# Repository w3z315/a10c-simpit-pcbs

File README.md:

# My A10C SimPit PCB collection

Welcome to the A10C Simpit Projects repository! This repository contains all the PCB designs and DCS-Bios Arduino code for various components of an A10C Simpit, currently including the UFC (Up-Front Controller) and MFCD (Multi-Function Color Display).

## Sponsorship
Thank you so much PCBWay.com for sponsoring parts of this project! I was genuinely surprised by how quickly the PCBs arrived - in just 9 days, without even opting for the very express shipping variant. The quality is outstanding, and the PCBs work flawlessly in my setup. It's been a fantastic experience, from design submission to receiving the boards ready for assembly.

## Projects

### UFC (Up-Front Controller)
- **[PCB Design](./ufc/pcb)**: Schematic, layout files, and Bill of Materials (BOM) for the UFC PCB.
- **[Arduino Code](./ufc/arduino)**: Source code and libraries for the UFC Arduino project.

### MFCD (Multi-Function Color Display)
- **[PCB Design](./mfcd/pcb)**: Schematic, layout files, and Bill of Materials (BOM) for the MFCD PCB.
- **[Arduino Code](./mfcd/arduino)**: Source code and libraries for the MFCD Arduino project.

## Getting Started

To get started with any of the projects, navigate to the respective directories for detailed instructions and files.

### Prerequisites

- [KiCad ^8.0](https://www.kicad.org/) for viewing and editing PCB files.
- [PlatformIO](https://platformio.org/)
- [DCS-BIOS - Skunkworks Fork](https://github.com/DCS-Skunkworks/dcs-bios)

### Installation

1. Clone the repository:
    ```sh
    git clone https://github.com/w3z315/a10c-simpit-pcbs.git
    cd a10c-simpit-pcbs
    ```

2. Follow the instructions in the respective project directories to set up the PCB or Arduino code.

## Documentation

Additional documentation can be found in the wiki.

## Contributing

Contributions are welcome! 

## License

This project is licensed under the GPL 3 License. See the [LICENSE](./LICENSE) file for details.

## Acknowledgments

- Thanks to the open-source community for providing the tools and resources that made this project possible. (Winks to Kicad 8!)
- PCBWay.com for their sponsorship and assistance.
- A shoutout to all the DIYers and hobbyists who inspire me every day.
- TheWarthogProject.com - dude, you're amazing!

---

Feel free to reach out if you have any questions or need further assistance. Happy building!

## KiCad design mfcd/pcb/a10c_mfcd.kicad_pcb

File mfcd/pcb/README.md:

# MFCD (Multi-Function-Color-Display) PCB

This one is still work in progress.

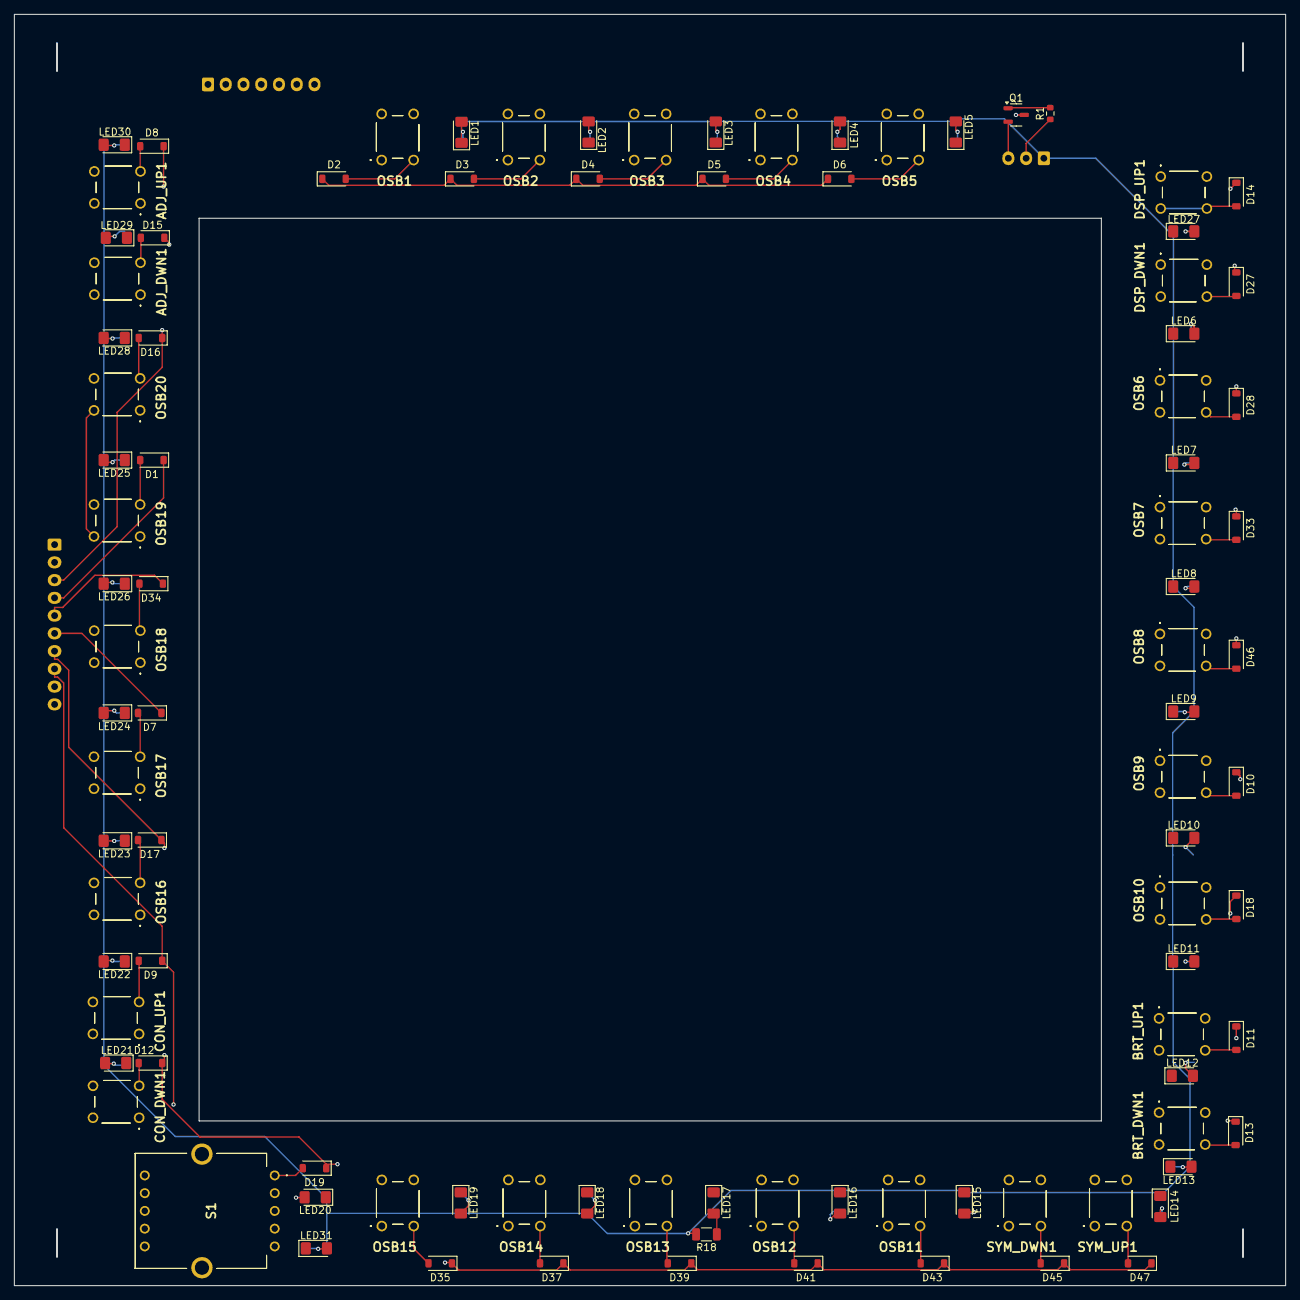
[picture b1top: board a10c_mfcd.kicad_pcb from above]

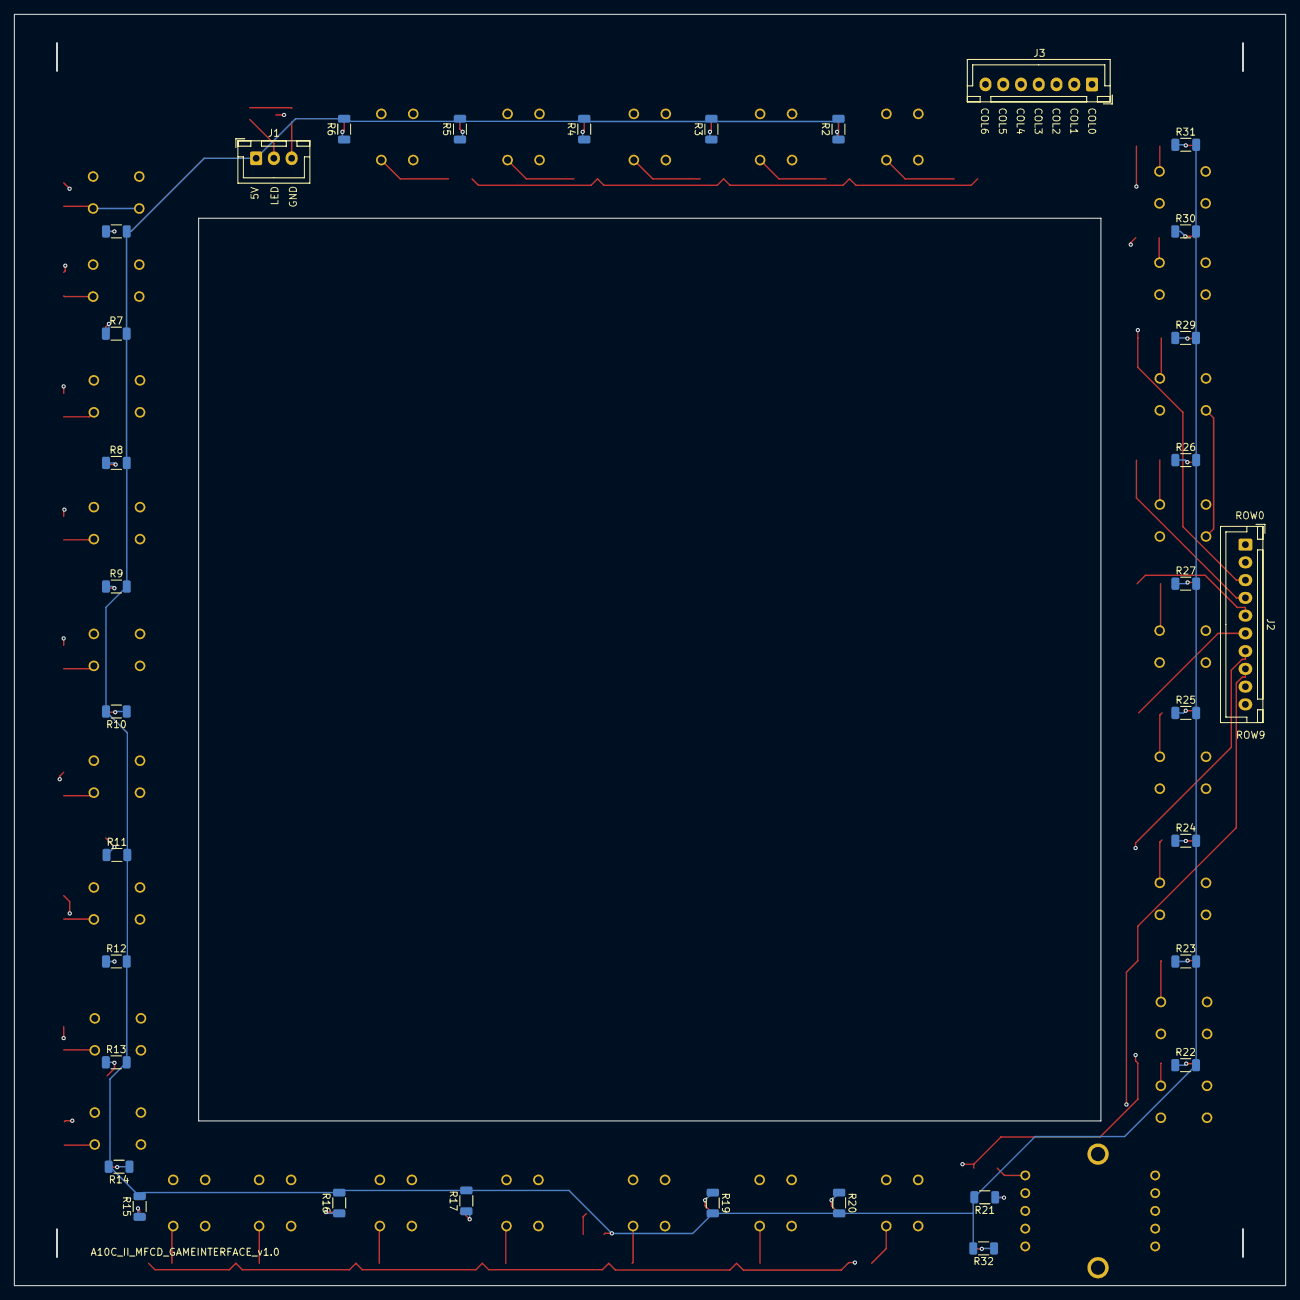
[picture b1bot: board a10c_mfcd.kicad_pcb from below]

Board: 4 copper layers, 179.0 x 179.0 mm, 129 parts (33 on the bottom side), 84 nets.

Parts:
ADJ_DWN1: Switch; 18259671
ADJ_UP1: Switch; 18259671
BRT_DWN1: Switch; 18259671
BRT_UP1: Switch; 18259671
CON_DWN1: Switch; 18259671
CON_UP1: Switch; 18259671
D1, D2, D3, D4, D5, D6, D7, D8, D9, D10, D11, D12, D13, D14, D15, D16, D17, D18, D19, D27, D28, D33, D34, D35, D37, D39, D41, D43, D45, D46, D47: D_Small; D_SOD-123
DSP_DWN1: Switch; 18259671
DSP_UP1: Switch; 18259671
J1: Conn_LED; JST_XH_B3B-XH-A_1x03_P2.50mm_Vertical
J2: Conn_ROWS; JST_XH_B10B-XH-A_1x10_P2.50mm_Vertical
J3: Conn_COLS; JST_XH_B7B-XH-A_1x07_P2.50mm_Vertical
LED1, LED2, LED3, LED4, LED5, LED6, LED7, LED8, LED9, LED10, LED11, LED12, LED13, LED14, LED15, LED16, LED17, LED18, LED19, LED20, LED21, LED22, LED23, LED24, LED25, LED26, LED27, LED28, LED29, LED30, LED31: 1206; LED_1206_3216Metric_Pad1.42x1.75mm_HandSolder
OSB1, OSB2, OSB3, OSB4, OSB5, OSB6, OSB7, OSB8, OSB9, OSB10, OSB11, OSB12, OSB13, OSB14, OSB15, OSB16, OSB17, OSB18, OSB19, OSB20: Switch; 18259671
Q1: BC817-25LT1G; SOT-23-3
R1: 1000; R_0603_1608Metric
R2, R3, R4, R5, R6, R7, R8, R9, R10, R11, R12, R13, R14, R15, R16, R17, R18, R19, R20, R21, R22, R23, R24, R25, R26, R27, R28, R29, R30, R31, R32: 270; R_1206_3216Metric
S1: SRBV131502
SYM_DWN1: Switch; 18259671
SYM_UP1: Switch; 18259671

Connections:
5V: J1.1, R2.2, R3.2, R4.2, R5.2, R6.2, R7.2, R8.2, R9.2, R10.2, R11.2, R12.2, R13.2, R14.2, R15.2, R16.2, R17.2, R18.2, R19.2, R20.2, R21.2, R22.2, R23.2, R24.2, R25.2, R26.2, R27.2, R28.2, R29.2, R30.2, R31.2, R32.2
COL0: ADJ_DWN1.1, ADJ_UP1.1, CON_DWN1.1, CON_UP1.1, J3.1, OSB15.1, OSB16.1, OSB17.1, OSB18.1, OSB19.1, OSB20.1
COL1: J3.2, OSB1.1, OSB14.1, S1.2 (NO_1)
COL2: J3.3, OSB2.1, OSB13.1, S1.3 (NO_2)
COL3: J3.4, OSB3.1, OSB12.1, S1.4 (NO_3)
COL4: J3.5, OSB4.1, OSB11.1
COL5: J3.6, OSB5.1, SYM_DWN1.1
COL6: BRT_DWN1.1, BRT_UP1.1, DSP_DWN1.1, DSP_UP1.1, J3.7, OSB6.1, OSB7.1, OSB8.1, OSB9.1, OSB10.1, SYM_UP1.1
GND: J1.3, Q1.2 (EMITTER)
LED: J1.2, R1.1
unnamed: D1.2 (A), OSB19.2
unnamed: D2.2 (A), OSB1.2
unnamed: D2.1 (K), D3.1 (K), D4.1 (K), D5.1 (K), D6.1 (K)
unnamed: D3.2 (A), OSB2.2
unnamed: D4.2 (A), OSB3.2
unnamed: D5.2 (A), OSB4.2
unnamed: D6.2 (A), OSB5.2
unnamed: D7.2 (A), OSB17.2
unnamed: ADJ_UP1.2, D8.2 (A)
unnamed: CON_UP1.2, D9.2 (A)
unnamed: D10.2 (A), OSB9.2
unnamed: BRT_UP1.2, D11.2 (A)
unnamed: CON_DWN1.2, D12.2 (A)
unnamed: BRT_DWN1.2, D13.2 (A)
unnamed: D14.2 (A), DSP_UP1.2
unnamed: ADJ_DWN1.2, D15.2 (A)
unnamed: D16.2 (A), OSB20.2
unnamed: D17.2 (A), OSB16.2
unnamed: D18.2 (A), OSB10.2
unnamed: D19.2 (A), S1.1 (C)
unnamed: D27.2 (A), DSP_DWN1.2
unnamed: D28.2 (A), OSB6.2
unnamed: D33.2 (A), OSB7.2
unnamed: D34.2 (A), OSB18.2
unnamed: D35.2 (A), OSB15.2
unnamed: D37.2 (A), OSB14.2
unnamed: D39.2 (A), OSB13.2
unnamed: D41.2 (A), OSB12.2
unnamed: D43.2 (A), OSB11.2
unnamed: D45.2 (A), SYM_DWN1.2
unnamed: D46.2 (A), OSB8.2
unnamed: D47.2 (A), SYM_UP1.2
unnamed: LED1.1 (K), LED1.2 (A), Q1.3 (COLLECTOR), R2.1
unnamed: LED2.2 (A), R3.1
unnamed: LED3.2 (A), R4.1
unnamed: LED4.2 (A), R5.1
unnamed: LED5.2 (A), R6.1
unnamed: LED6.2 (A), R7.1
unnamed: LED7.2 (A), R8.1
unnamed: LED8.2 (A), R9.1
unnamed: LED9.2 (A), R10.1
unnamed: LED10.2 (A), R11.1
unnamed: LED11.2 (A), R12.1
unnamed: LED12.2 (A), R13.1
unnamed: LED13.2 (A), R14.1
unnamed: LED14.2 (A), R15.1
unnamed: LED15.2 (A), R16.1
unnamed: LED16.2 (A), R17.1
unnamed: LED17.2 (A), R18.1
unnamed: LED18.2 (A), R19.1
unnamed: LED19.2 (A), R20.1
unnamed: LED20.2 (A), R21.1
unnamed: LED21.2 (A), R22.1
unnamed: LED22.2 (A), R23.1
unnamed: LED23.2 (A), R24.1
unnamed: LED24.2 (A), R25.1
unnamed: LED25.2 (A), R26.1
unnamed: LED26.2 (A), R27.1
unnamed: LED27.2 (A), R28.1
unnamed: LED28.2 (A), R29.1
unnamed: LED29.2 (A), R30.1
unnamed: LED30.2 (A), R31.1
unnamed: LED31.2 (A), R32.1
unnamed: Q1.1 (BASE), R1.2
ROW0: D8.1 (K), D14.1 (K), J2.1
ROW1: D15.1 (K), D27.1 (K), J2.2
ROW2: D16.1 (K), D28.1 (K), J2.3
ROW3: D1.1 (K), D33.1 (K), J2.4
ROW4: D34.1 (K), D46.1 (K), J2.5
ROW5: D7.1 (K), D10.1 (K), J2.6
ROW6: D17.1 (K), D18.1 (K), J2.7
ROW7: D9.1 (K), D11.1 (K), J2.8
ROW8: D12.1 (K), D13.1 (K), D19.1 (K), J2.9
ROW9: D35.1 (K), D37.1 (K), D39.1 (K), D41.1 (K), D43.1 (K), D45.1 (K), D47.1 (K), J2.10

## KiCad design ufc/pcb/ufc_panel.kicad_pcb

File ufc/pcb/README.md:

# A-10C Upfront Control Panel (UFC) PCB

Welcome to the repository for my very first PCB design, crafted specifically for an A-10C cockpit simulator project. This project has been a labor of love, a lot of learning, and yes, a few missteps - but that's the beauty of DIY!

## Demo Video

Check out the demo video to see the A10C UFC in action:

## Sponsorship
Thank you so much [PCBWay.com](https://pcbway.com) for sponsoring this project! I was genuinely surprised by how quickly the PCBs arrived - in just 9 days, without even opting for the very express shipping variant. The quality is outstanding, and the PCBs work flawlessly in my setup. It's been a fantastic experience, from design submission to receiving the boards ready for assembly.

## About the Project
The A-10C UFC PCB is for my custom A-10C cockpit control panel.

## Todos:
- [ ] Add more backlight LEDs so the bottom row is better illuminated.
- [ ] Add another yellow LED for the Master Caution to spread out light more evenly.
- [ ] Better connector?

## Arduino Code
You can find the code for the PCB and Arduino Nano at [https://github.com/w3z315/a10c-ufc-arduino](https://github.com/w3z315/a10c-ufc-arduino).

## Repository Contents
Inside this repository, you'll find all the KiCad files used to create the PCB. Feel free to browse through them, use them as a reference, or even contribute to improving the design.

## Images & gifs

)

## Issues and Contributing
If you notice any issues or if you've got suggestions for improvements, don't hesitate to open an issue or a pull request. This project is all about community and collaboration.

## License

This project is licensed under the GNU GPLv3 License - see the [LICENSE](LICENSE) file for details.

## Acknowledgements
- Thanks to the open-source community for providing the tools and resources that made this project possible. (Winks to Kicad 8!)
- PCBWay.com for their sponsorship and assistance.
- A shoutout to all the DIYers and hobbyists who inspire me every day.
- TheWarthogProject.com - dude, you're amazing!

Happy building!

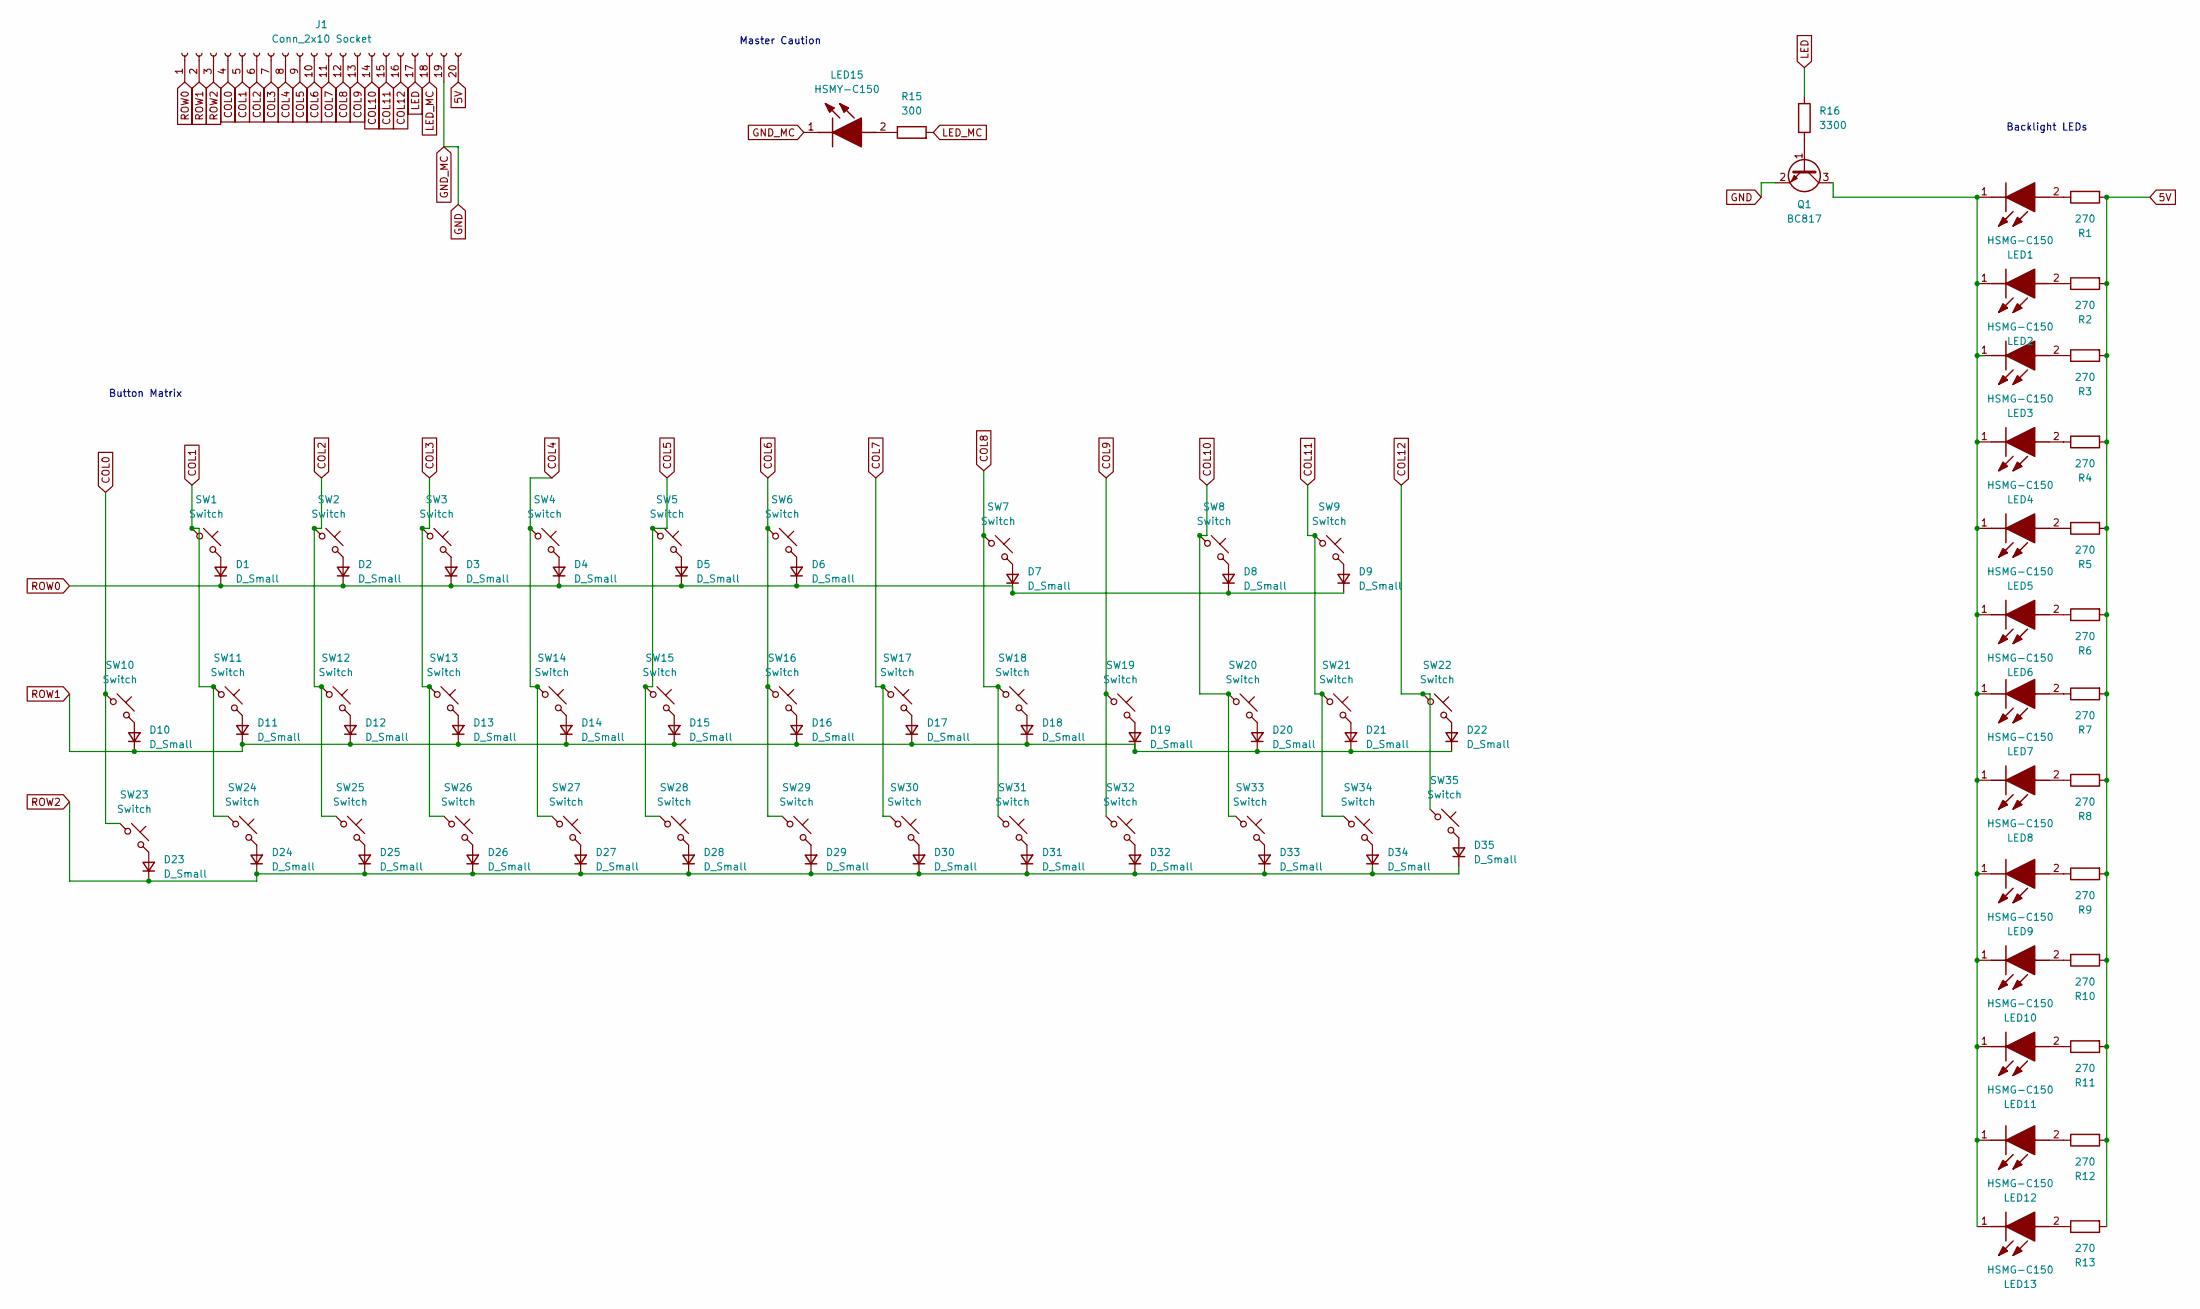
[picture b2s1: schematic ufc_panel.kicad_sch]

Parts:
D1, D2, D3, D4, D5, D6, D7, D8, D9, D10, D11, D12, D13, D14, D15, D16, D17, D18, D19, D20, D21, D22, D23, D24, D25, D26, D27, D28, D29, D30, D31, D32, D33, D34, D35: D_Small; D_SOD-123
J1: Conn_2x10 Socket; PinHeader_1x20_P2.54mm_Vertical
LED1, LED2, LED3, LED4, LED5, LED6, LED7, LED8, LED9, LED10, LED11, LED12, LED13: HSMG-C150; LED_1206_3216Metric_Pad1.42x1.75mm_HandSolder; Mouser Part Number 630-HSMG-C150
LED15: HSMY-C150; LED_1206_3216Metric_Pad1.42x1.75mm_HandSolder; Mouser Part Number 630-HSMY-C150
Q1: BC817; SOT-23
R1, R2, R3, R4, R5, R6, R7, R8, R9, R10, R11, R12, R13: 270; R_1206_3216Metric
R15: 300; R_1206_3216Metric
R16: 3300; R_0603_1608Metric
SW1, SW2, SW3, SW4, SW5, SW6, SW7, SW8, SW9, SW10, SW11, SW12, SW13, SW14, SW15, SW16, SW17, SW18, SW19, SW20, SW21, SW22, SW23, SW24, SW25, SW26, SW27, SW28, SW29, SW30, SW31, SW32, SW33, SW34, SW35: Switch; SW_PUSH_6mm_H4.3mm_INT_CONNECTED

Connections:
5V: J1.20, R1.2, R2.2, R3.2, R4.2, R5.2, R6.2, R7.2, R8.2, R9.2, R10.2, R11.2, R12.2, R13.2
COL0: J1.4, SW10.1, SW23.1
COL1: J1.5, SW1.1, SW11.1, SW24.1
COL2: J1.6, SW2.1, SW12.1, SW25.1
COL3: J1.7, SW3.1, SW13.1, SW26.1
COL4: J1.8, SW4.1, SW14.1, SW27.1
COL5: J1.9, SW5.1, SW15.1, SW28.1
COL6: J1.10, SW6.1, SW16.1, SW29.1
COL7: J1.11, SW17.1, SW30.1
COL8: J1.12, SW7.1, SW18.1, SW31.1
COL9: J1.13, SW19.1, SW32.1
COL10: J1.14, SW8.1, SW20.1, SW33.1
COL11: J1.15, SW9.1, SW21.1, SW34.1
COL12: J1.16, SW22.1, SW35.1
GND: J1.19, LED15.1 (K), Q1.2 (E)
LED: J1.17, R16.1
LED_MC: J1.18, R15.2
unnamed: D1.2 (A), SW1.2
unnamed: D2.2 (A), SW2.2
unnamed: D3.2 (A), SW3.2
unnamed: D4.2 (A), SW4.2
unnamed: D5.2 (A), SW5.2
unnamed: D6.2 (A), SW6.2
unnamed: D7.2 (A), SW7.2
unnamed: D8.2 (A), SW8.2
unnamed: D9.2 (A), SW9.2
unnamed: D10.2 (A), SW10.2
unnamed: D11.2 (A), SW11.2
unnamed: D12.2 (A), SW12.2
unnamed: D13.2 (A), SW13.2
unnamed: D14.2 (A), SW14.2
unnamed: D15.2 (A), SW15.2
unnamed: D16.2 (A), SW16.2
unnamed: D17.2 (A), SW17.2
unnamed: D18.2 (A), SW18.2
unnamed: D19.2 (A), SW19.2
unnamed: D20.2 (A), SW20.2
unnamed: D21.2 (A), SW21.2
unnamed: D22.2 (A), SW22.2
unnamed: D23.2 (A), SW23.2
unnamed: D24.2 (A), SW24.2
unnamed: D25.2 (A), SW25.2
unnamed: D26.2 (A), SW26.2
unnamed: D27.2 (A), SW27.2
unnamed: D28.2 (A), SW28.2
unnamed: D29.2 (A), SW29.2
unnamed: D30.2 (A), SW30.2
unnamed: D31.2 (A), SW31.2
unnamed: D32.2 (A), SW32.2
unnamed: D33.2 (A), SW33.2
unnamed: D34.2 (A), SW34.2
unnamed: D35.2 (A), SW35.2
unnamed: LED1.2 (A), R1.1
unnamed: LED1.1 (K), LED2.1 (K), LED3.1 (K), LED4.1 (K), LED5.1 (K), LED6.1 (K), LED7.1 (K), LED8.1 (K), LED9.1 (K), LED10.1 (K), LED11.1 (K), LED12.1 (K), LED13.1 (K), Q1.3 (C)
unnamed: LED2.2 (A), R2.1
unnamed: LED3.2 (A), R3.1
unnamed: LED4.2 (A), R4.1
unnamed: LED5.2 (A), R5.1
unnamed: LED6.2 (A), R6.1
unnamed: LED7.2 (A), R7.1
unnamed: LED8.2 (A), R8.1
unnamed: LED9.2 (A), R9.1
unnamed: LED10.2 (A), R10.1
unnamed: LED11.2 (A), R11.1
unnamed: LED12.2 (A), R12.1
unnamed: LED13.2 (A), R13.1
unnamed: LED15.2 (A), R15.1
unnamed: Q1.1 (B), R16.2
ROW0: D1.1 (K), D2.1 (K), D3.1 (K), D4.1 (K), D5.1 (K), D6.1 (K), D7.1 (K), D8.1 (K), D9.1 (K), J1.1
ROW1: D10.1 (K), D11.1 (K), D12.1 (K), D13.1 (K), D14.1 (K), D15.1 (K), D16.1 (K), D17.1 (K), D18.1 (K), D19.1 (K), D20.1 (K), D21.1 (K), D22.1 (K), J1.2
ROW2: D23.1 (K), D24.1 (K), D25.1 (K), D26.1 (K), D27.1 (K), D28.1 (K), D29.1 (K), D30.1 (K), D31.1 (K), D32.1 (K), D33.1 (K), D34.1 (K), D35.1 (K), J1.3

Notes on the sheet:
Button Matrix
Backlight LEDs
Master Caution

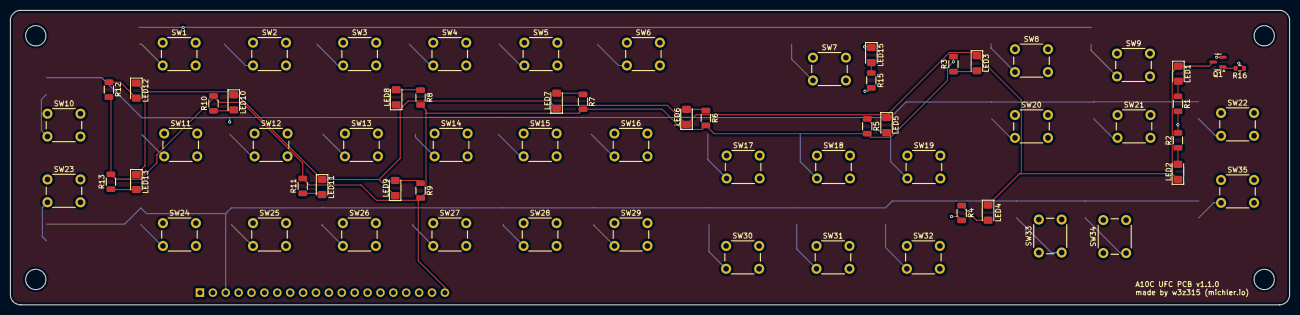
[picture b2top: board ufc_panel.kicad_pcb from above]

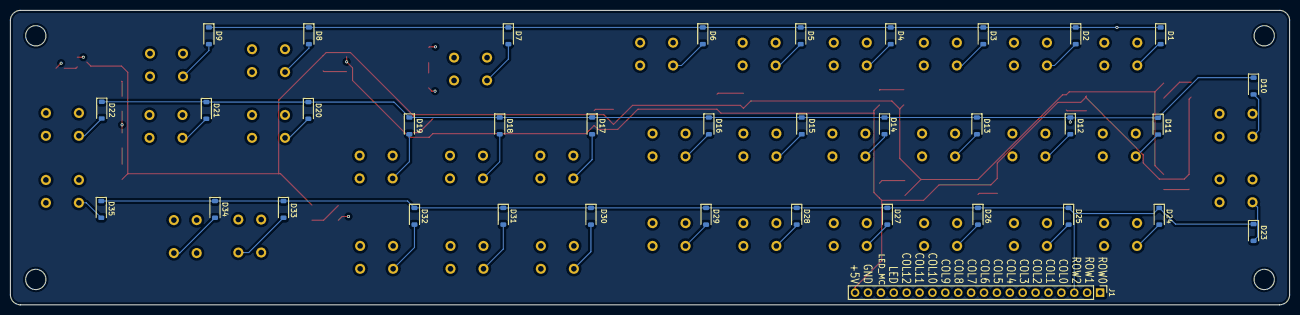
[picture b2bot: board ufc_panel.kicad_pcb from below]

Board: 4 copper layers, 252.0 x 58.0 mm, 101 parts (36 on the bottom side), 71 nets.

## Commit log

2024-05-25 chore: add temporary readme
2024-05-27 chore: merge other repositories to this one.
2024-05-28 feat(mfcd): updated whole layout to use JST
2024-05-28 fix(mfcd): remove lockfile, add .gitignore
2024-05-28 chore: add message to readme
2024-06-20 chore: update README
    Add hint for the altered DCS-BIOS-arduino-library.
2024-07-03 feat(mfcd): added initial arduino code
2024-07-07 feat(mfcd): add case for 3d printing
2024-07-07 chore(mfcd): add images to mfcd 3d printed case
